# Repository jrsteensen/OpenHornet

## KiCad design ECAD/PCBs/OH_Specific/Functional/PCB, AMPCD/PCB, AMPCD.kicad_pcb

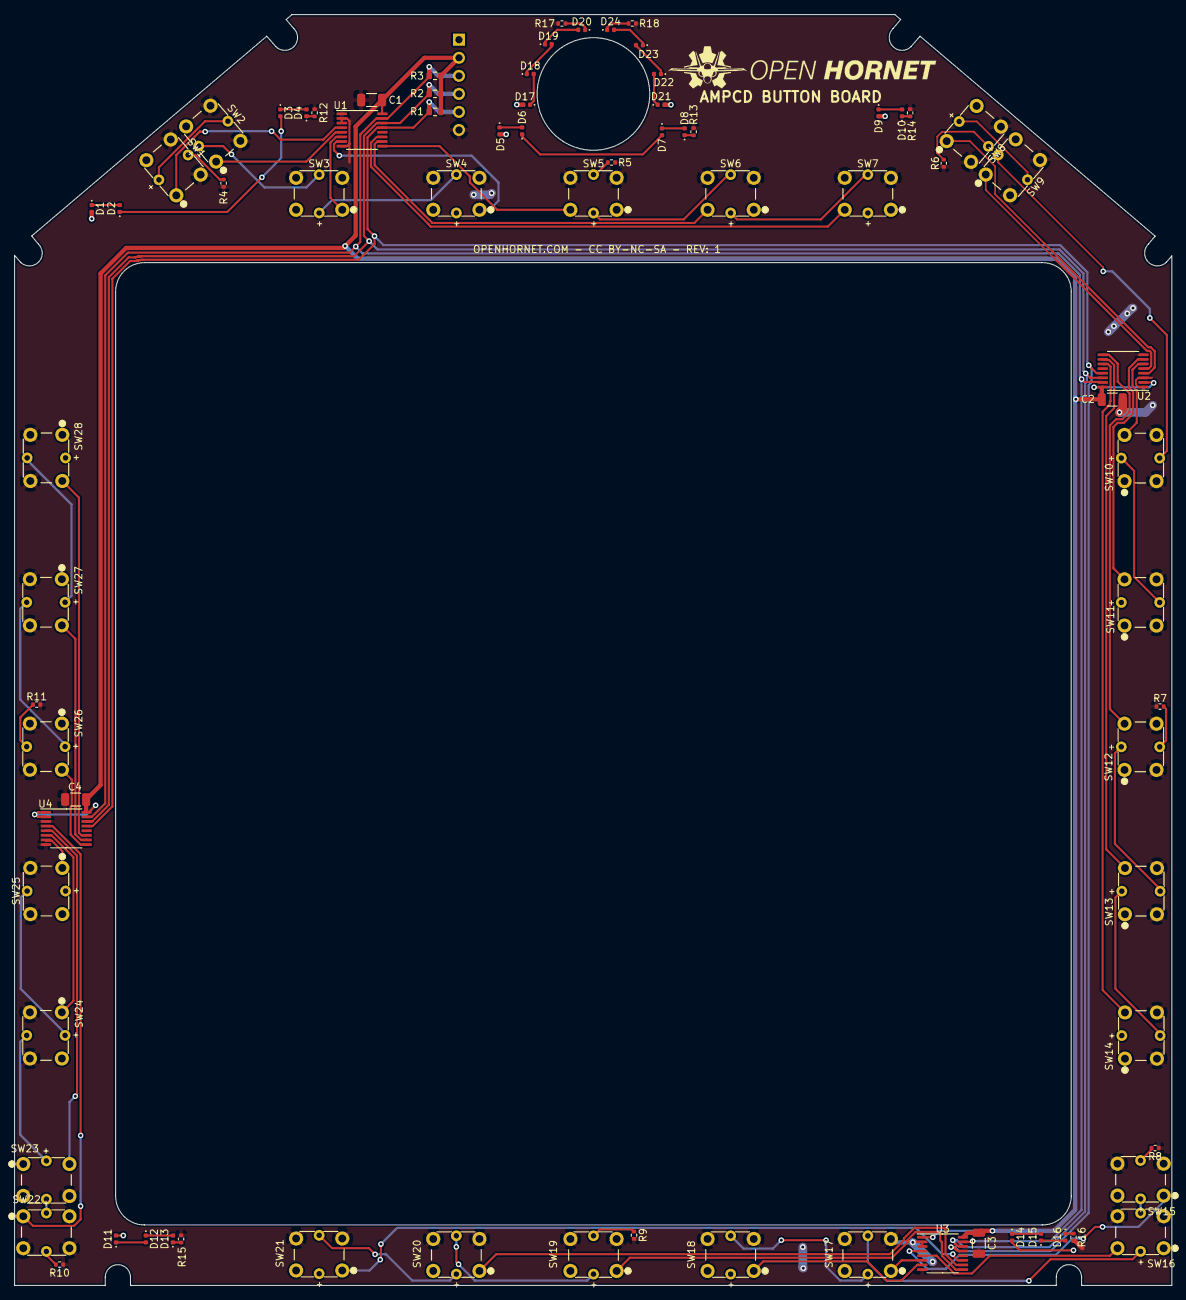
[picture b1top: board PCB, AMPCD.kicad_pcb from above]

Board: 2 copper layers, 162.9 x 178.9 mm, 79 parts (1 on the bottom side), 86 nets.

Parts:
C1, C2, C3, C4: 47uF; C_1206_3216Metric
D1, D2, D3, D4, D5, D6, D7, D8, D9, D10, D11, D12, D13, D14, D15, D16, D17, D18, D19, D20, D21, D22, D23, D24: LED; LED_0402_1005Metric
J1: Conn_01x06; PinHeader_1x06_P2.54mm_Horizontal
R1, R2, R3: 10K; R_0603_1608Metric
R4, R6, R8, R10, R12, R13, R17, R18: 33; R_0402_1005Metric
R5, R7, R9, R11, R15, R16: 150; R_0402_1005Metric
R14: 270; R_0402_1005Metric
SW1, SW2, SW3, SW4, SW5, SW6, SW7, SW8, SW9, SW10, SW11, SW12, SW13, SW14, SW15, SW16, SW17, SW18, SW19, SW20, SW21, SW22, SW23, SW24, SW25, SW26, SW27, SW28: TL1240GQ
U1, U2, U3, U4: TCA9554PWR; TSSOP-16_4.4x5mm_P0.65mm

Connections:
+5V: C1.1, C2.1, C3.1, C4.1, J1.2, R1.1, R2.1, R3.1, U1.16, U2.2, U2.16, U3.1, U3.16, U4.1, U4.2, U4.16
/U1P0: SW1.1, U1.4
/U1P1: SW2.1, U1.5
/U1P2: SW3.1, U1.6
/U1P3: SW4.1, U1.7
/U1P4: SW5.1, U1.9
/U1P5: SW6.1, U1.10
/U1P6: SW7.1, U1.11
/U2P0: SW8.1, U2.4
/U2P1: SW9.1, U2.5
/U2P2: SW10.1, U2.6
/U2P3: SW11.1, U2.7
/U2P4: SW12.1, U2.9
/U2P5: SW13.1, U2.10
/U2P6: SW14.1, U2.11
/U3P0: SW15.1, U3.4
/U3P1: SW16.1, U3.5
/U3P2: SW17.1, U3.6
/U3P3: SW18.1, U3.7
/U3P4: SW19.1, U3.9
/U3P5: SW20.1, U3.10
/U3P6: SW21.1, U3.11
/U4P0: SW22.1, U4.4
/U4P1: SW23.1, U4.5
/U4P2: SW24.1, U4.6
/U4P3: SW25.1, U4.7
/U4P4: SW26.1, U4.9
/U4P5: SW27.1, U4.10
/U4P6: SW28.1, U4.11
GND: C1.2, C2.2, C3.2, C4.2, J1.6, R4.1, R5.1, R6.1, R7.1, R8.1, R9.1, R10.1, R11.1, R12.2, R13.2, R14.2, R15.2, R16.2, R17.2, R18.2, SW1.2, SW2.2, SW3.2, SW4.2, SW5.2, SW6.2, SW7.2, SW8.2, SW9.2, SW10.2, SW11.2, SW12.2, SW13.2, SW14.2, SW15.2, SW16.2, SW17.2, SW18.2, SW19.2, SW20.2, SW21.2, SW22.2, SW23.2, SW24.2, SW25.2, SW26.2, SW27.2, SW28.2, U1.1, U1.2, U1.3, U1.8, U2.1, U2.3, U2.8, U3.2, U3.3, U3.8, U4.3, U4.8
IRQ: J1.5, R1.2, U1.13, U2.13, U3.13, U4.13
unnamed: D1.1, D2.2
unnamed: D2.1, D3.2
unnamed: D3.1, D4.2
unnamed: D4.1, R12.1
unnamed: D5.1, D6.2
unnamed: D6.1, D7.2
unnamed: D7.1, D8.2
unnamed: D8.1, R13.1
unnamed: D10.1, R14.1
unnamed: D9.1, D10.2
unnamed: D11.1, D12.2
unnamed: D12.1, D13.2
unnamed: D13.1, R15.1
unnamed: D14.1, D15.2
unnamed: D15.1, D16.2
unnamed: D16.1, R16.1
unnamed: D17.1, D18.2
unnamed: D18.1, D19.2
unnamed: D19.1, D20.2
unnamed: D20.1, R17.1
unnamed: D21.1, D22.2
unnamed: D22.1, D23.2
unnamed: D23.1, D24.2
unnamed: D24.1, R18.1
unnamed: R4.2, SW1.3
unnamed: R5.2, SW5.3
unnamed: R6.2, SW8.3
unnamed: R7.2, SW12.3
unnamed: R8.2, SW15.3
unnamed: R9.2, SW19.3
unnamed: R10.2, SW22.3
unnamed: R11.2, SW26.3
unnamed: SW1.4, SW2.3
unnamed: SW2.4, SW3.3
unnamed: SW3.4, SW4.3
unnamed: SW5.4, SW6.3
unnamed: SW6.4, SW7.3
unnamed: SW8.4, SW9.3
unnamed: SW9.4, SW10.3
unnamed: SW10.4, SW11.3
unnamed: SW12.4, SW13.3
unnamed: SW13.4, SW14.3
unnamed: SW15.4, SW16.3
unnamed: SW16.4, SW17.3
unnamed: SW17.4, SW18.3
unnamed: SW19.4, SW20.3
unnamed: SW20.4, SW21.3
unnamed: SW22.4, SW23.3
unnamed: SW23.4, SW24.3
unnamed: SW24.4, SW25.3
unnamed: SW26.4, SW27.3
unnamed: SW27.4, SW28.3
SCL: J1.4, R2.2, U1.14, U2.14, U3.14, U4.14
SDA: J1.3, R3.2, U1.15, U2.15, U3.15, U4.15
VCC: D1.2, D5.2, D9.2, D11.2, D14.2, D17.2, D21.2, J1.1, SW4.4, SW7.4, SW11.4, SW14.4, SW18.4, SW21.4, SW25.4, SW28.4

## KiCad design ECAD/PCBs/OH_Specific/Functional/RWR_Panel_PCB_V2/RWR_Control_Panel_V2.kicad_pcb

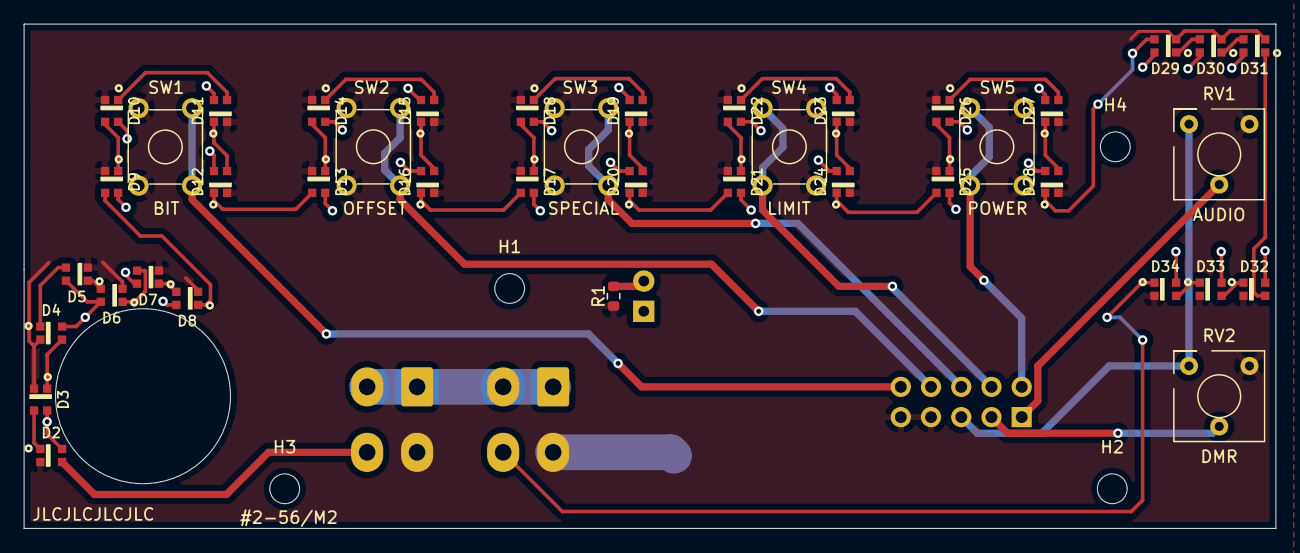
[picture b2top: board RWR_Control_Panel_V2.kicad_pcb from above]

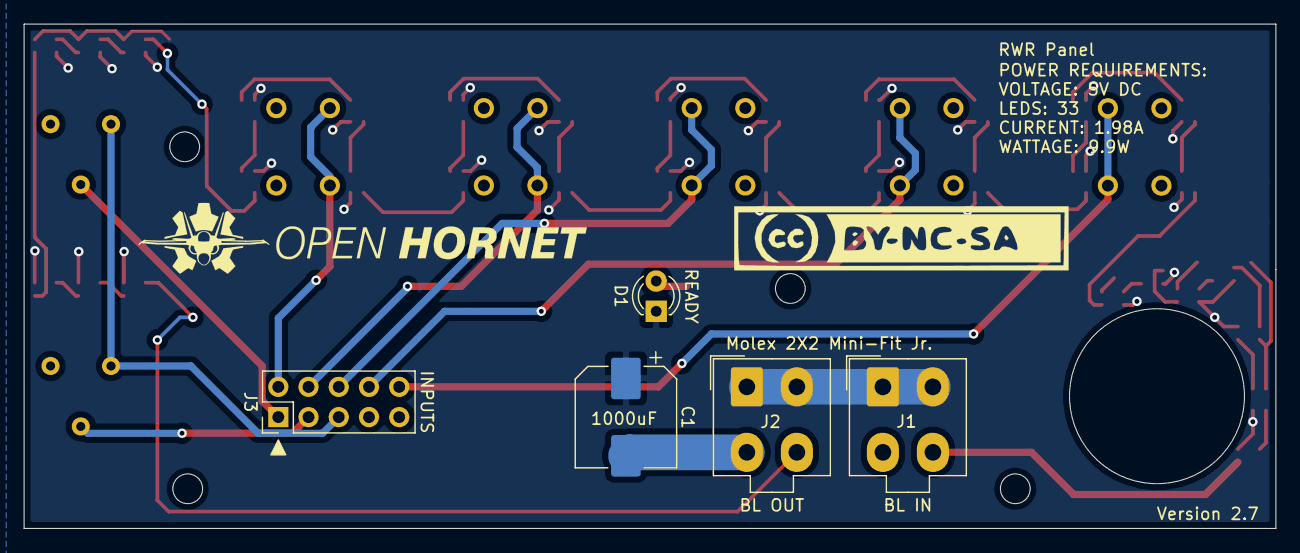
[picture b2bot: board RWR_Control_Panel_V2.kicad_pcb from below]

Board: 2 copper layers, 105.2 x 42.4 mm, 50 parts (5 on the bottom side), 45 nets.

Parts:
C1: 1000 nF; CP_Elec_8x10
D1: READY; LED_D3.0mm
D2, D3, D4, D5, D6, D7, D8, D9, D10, D11, D12, D13, D14, D15, D16, D17, D18, D19, D20, D21, D22, D23, D24, D25, D26, D27, D28, D29, D30, D31, D32, D33, D34: LED; WS2812-2020
H1, H2, H3, H4: MountingHole; MountingHole_2.5mm
J1: BL IN; Molex_Mini-Fit_Jr_5566-04A_2x02_P4.20mm_Vertical
J2: BL OUT; Molex_Mini-Fit_Jr_5566-04A_2x02_P4.20mm_Vertical
J3: INPUTS; PinHeader_2x05_P2.54mm_Vertical
R1: R; R_0603_1608Metric
RV1: AUDIO; Bourns_3310Y
RV2: DMR; Bourns_3310Y
SW1: BIT; SW_TH_Tactile_Omron_B3F-10xx
SW2: OFFSET; SW_TH_Tactile_Omron_B3F-10xx
SW3: SPECIAL; SW_TH_Tactile_Omron_B3F-10xx
SW4: LIMIT; SW_TH_Tactile_Omron_B3F-10xx
SW5: POWER; SW_TH_Tactile_Omron_B3F-10xx

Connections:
+5V: J3.5, RV1.1, RV2.1
/A_AUDIO: J3.1, RV1.2
/A_DMR: J3.3, RV2.2
/BIT_SW: J3.10, SW1.1, SW1.2
/BL_+5V: C1.1, D1.1, D2.4, D3.4, D4.4, D5.4, D6.4, D7.4, D8.4, D9.4, D10.4, D11.4, D12.4, D13.4, D14.4, D15.4, D16.4, D17.4, D18.4, D19.4, D20.4, D21.4, D22.4, D23.4, D24.4, D25.4, D26.4, D27.4, D28.4, D29.4, D30.4, D31.4, D32.4, D33.4, D34.4, J1.1, J1.2, J2.1, J2.2
/BL_DATA1: D9.1, D10.3
/BL_DATA2: D17.1, D18.3
/BL_DATA3: D25.1, D26.3
/BL_DATA4: D33.1, D34.3
/BL_DIN: D2.3, J1.4
/BL_DOUT: D34.1, J2.4
/LIMIT_SW: J3.4, SW4.1, SW4.2
/OFFSET_SW: J3.8, SW2.1, SW2.2
/POWER_SW: J3.2, SW5.1, SW5.2
/SPECIAL_SW: J3.6, SW3.1, SW3.2
GND: C1.2, D2.2, D3.2, D4.2, D5.2, D6.2, D7.2, D8.2, D9.2, D10.2, D11.2, D12.2, D13.2, D14.2, D15.2, D16.2, D17.2, D18.2, D19.2, D20.2, D21.2, D22.2, D23.2, D24.2, D25.2, D26.2, D27.2, D28.2, D29.2, D30.2, D31.2, D32.2, D33.2, D34.2, J1.3, J2.3, J3.7, J3.9, R1.2, RV1.3, RV2.3, SW1.3, SW1.4, SW2.3, SW2.4, SW3.3, SW3.4, SW4.3, SW4.4, SW5.3, SW5.4
unnamed: D1.2, R1.1
unnamed: D2.1, D3.3
unnamed: D3.1, D4.3
unnamed: D4.1, D5.3
unnamed: D5.1, D6.3
unnamed: D6.1, D7.3
unnamed: D7.1, D8.3
unnamed: D8.1, D9.3
unnamed: D10.1, D11.3
unnamed: D11.1, D12.3
unnamed: D12.1, D13.3
unnamed: D13.1, D14.3
unnamed: D14.1, D15.3
unnamed: D15.1, D16.3
unnamed: D16.1, D17.3
unnamed: D18.1, D19.3
unnamed: D19.1, D20.3
unnamed: D20.1, D21.3
unnamed: D21.1, D22.3
unnamed: D22.1, D23.3
unnamed: D23.1, D24.3
unnamed: D24.1, D25.3
unnamed: D26.1, D27.3
unnamed: D27.1, D28.3
unnamed: D28.1, D29.3
unnamed: D29.1, D30.3
unnamed: D30.1, D31.3
unnamed: D31.1, D32.3
unnamed: D32.1, D33.3

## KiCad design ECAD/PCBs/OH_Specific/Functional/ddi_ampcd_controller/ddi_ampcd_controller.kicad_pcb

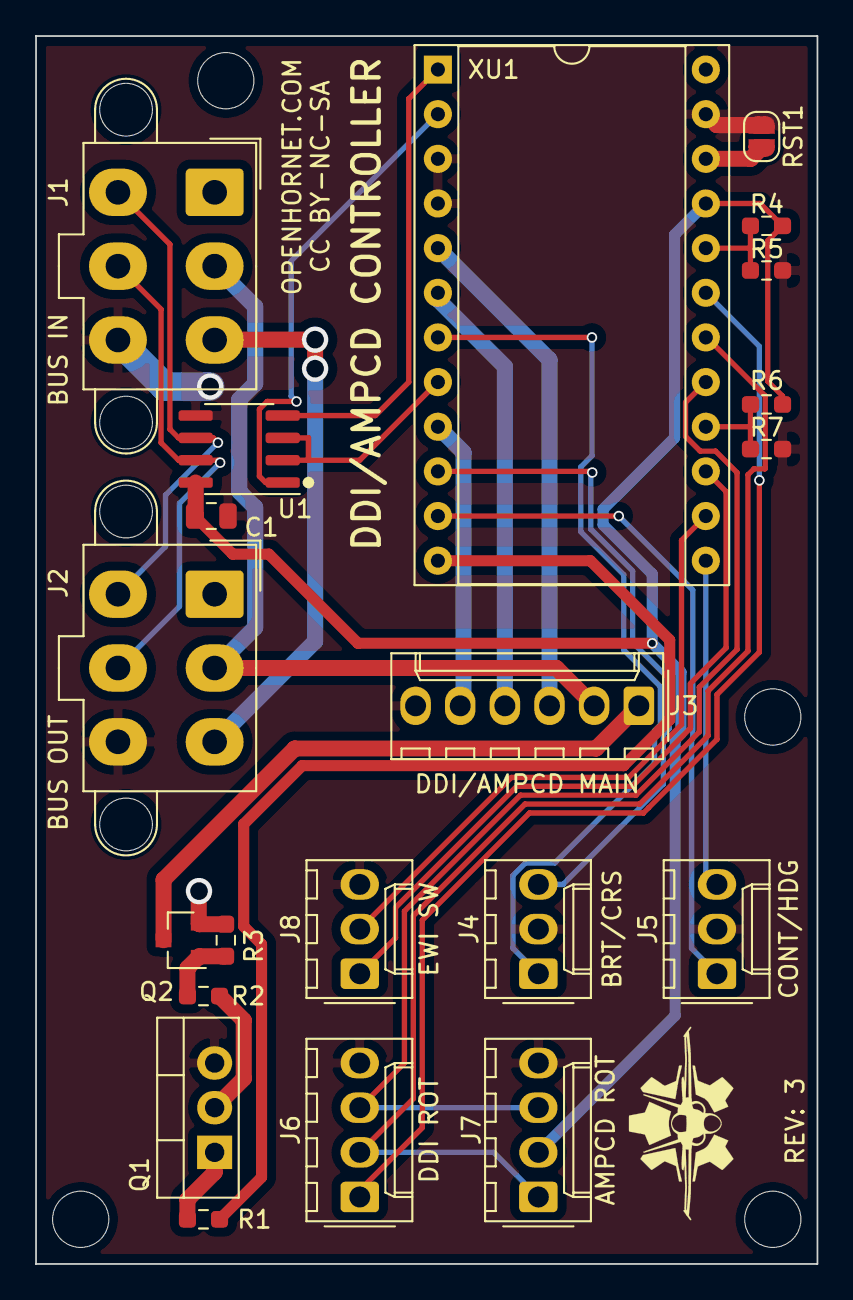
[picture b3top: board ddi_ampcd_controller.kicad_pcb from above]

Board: 2 copper layers, 44.5 x 69.8 mm, 25 parts (0 on the bottom side), 30 nets.

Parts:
C1: 0.1uF; C_0805_2012Metric
H1, H2, H3, H4: MountingHole; MountingHole_3.2mm_M3
J1: BUS IN; Molex_Mini-Fit_Jr_5566-06A2_2x03_P4.20mm_Vertical
J2: BUS OUT; Molex_Mini-Fit_Jr_5566-06A2_2x03_P4.20mm_Vertical
J3: DDI/AMPCD MAIN; Molex_KK-254_AE-6410-06A_1x06_P2.54mm_Vertical
J4: BRT/CRS; Molex_KK-254_AE-6410-03A_1x03_P2.54mm_Vertical
J5: CONT/HDG; Molex_KK-254_AE-6410-03A_1x03_P2.54mm_Vertical
J6: DDI ROT; Molex_KK-254_AE-6410-04A_1x04_P2.54mm_Vertical
J7: AMPCD ROT; Molex_KK-254_AE-6410-04A_1x04_P2.54mm_Vertical
J8: EWI SW; Molex_KK-254_AE-6410-03A_1x03_P2.54mm_Vertical
Q1: IRFB3206PBF; TO-220-3_Vertical
Q2: IRLML6402TRPBF; SOT-23
R1, R2, R3, R4, R5, R6, R7: 10K; R_0603_1608Metric_Pad0.98x0.95mm_HandSolder
RST1: RST; SolderJumper-2_P1.3mm_Open_RoundedPad1.0x1.5mm
U1: MAX487EESA+T; SOIC-8_3.9x4.9mm_P1.27mm
XU1: ProMicro_5V/16Hz; DIP-24_W15.24mm_Socket

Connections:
+5V: C1.1, J7.2, R4.2, R6.2, U1.8, XU1.21
/+3.3V_SUPPLY: J1.3, J2.3
/+5V_SUPPLY: J1.2, J2.2, J3.2
/+12V_PWM: J3.1, Q2.3
/+12V_SUPPLY: J1.1, J2.1, Q2.2, R3.2, XU1.24
/A0: J6.3, J7.3, XU1.17
/A1: J6.2, J7.1, XU1.18
/A2: J6.1, XU1.19
/A3: R4.1, R5.2, XU1.20
/BUS-A: J1.4, J2.4, U1.6
/BUS-B: J1.5, J2.5, U1.7
/D4_A6: J4.1, XU1.7
/D7: J4.3, XU1.10
/D8_A8: J5.1, XU1.11
/D14_MISO: J8.1, XU1.15
/D15_SCK: R6.1, R7.2, XU1.16
/D16_MOSI: J8.2, XU1.14
/RST: RST1.2, XU1.22
/RX1_D0: U1.1, XU1.2
/SDA_D2: J3.3, XU1.5
/TX0_D1: U1.4, XU1.1
/~D5: U1.2, U1.3, XU1.8
/~D6_A7: J3.5, XU1.9
/~D9_A9: R1.1, XU1.12
/~D10_A10: J5.3, XU1.13
/~SCL_D3: J3.4, XU1.6
GND: C1.2, J1.6, J2.6, J3.6, J4.2, J5.2, J6.4, J7.4, J8.3, Q1.3, R5.1, R7.1, RST1.1, U1.5, XU1.3, XU1.4, XU1.23
unnamed: Q1.1, R1.2
unnamed: Q1.2, R2.2
unnamed: Q2.1, R2.1, R3.1

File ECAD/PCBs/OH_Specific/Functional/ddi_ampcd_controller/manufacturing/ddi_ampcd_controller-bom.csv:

Comment,Designator,Footprint,LCSC
"0.1uF","C1","Capacitor_SMD:C_0805_2012Metric_Pad1.15x1.40mm_HandSolder","C49678"
"MountingHole","H1,H2,H3,H4","MountingHole:MountingHole_3.2mm_M3",""
"BUS IN","J1","Connector_Molex:Molex_Mini-Fit_Jr_5569-06A1_2x03_P4.20mm_Horizontal",""
"BUS OUT","J2","Connector_Molex:Molex_Mini-Fit_Jr_5569-06A1_2x03_P4.20mm_Horizontal",""
"Conn_01x06","J3","Connector_Molex:Molex_KK-254_AE-6410-06A_1x06_P2.54mm_Vertical",""
"BRT/CRS","J4","Connector_Molex:Molex_KK-254_AE-6410-03A_1x03_P2.54mm_Vertical",""
"CONT/HDG","J5","Connector_Molex:Molex_KK-254_AE-6410-03A_1x03_P2.54mm_Vertical",""
"DDI ROT","J6","Connector_PinHeader_2.54mm:PinHeader_1x04_P2.54mm_Vertical",""
"AMPCD ROT","J7","Connector_PinHeader_2.54mm:PinHeader_1x04_P2.54mm_Vertical",""
"Digital","P1","Connector_PinSocket_2.54mm:PinSocket_1x15_P2.54mm_Vertical",""
"Analog","P2","Connector_PinSocket_2.54mm:PinSocket_1x15_P2.54mm_Vertical",""
"IRFB3206PBF","Q1","Package_TO_SOT_THT:TO-220-3_Vertical","C2642"
"IRLML6402TRPBF","Q2","Package_TO_SOT_SMD:SOT-23","C2593"
"10K","R1,R2,R3,R4,R5,R6,R7","Resistor_SMD:R_0603_1608Metric_Pad0.98x0.95mm_HandSolder","C25804"
"TP-12","TP1","TestPoint:TestPoint_THTPad_D1.5mm_Drill0.7mm",""
"TP-5V","TP2","TestPoint:TestPoint_THTPad_D1.5mm_Drill0.7mm",""
"TP-3.3V","TP3","TestPoint:TestPoint_THTPad_D1.5mm_Drill0.7mm",""
"TP-GND","TP4","TestPoint:TestPoint_THTPad_D1.5mm_Drill0.7mm",""
"TP-A","TP5","TestPoint:TestPoint_THTPad_D1.5mm_Drill0.7mm",""
"TP-B","TP6","TestPoint:TestPoint_THTPad_D1.5mm_Drill0.7mm",""
"MAX487EESA+T","U1","Package_SO:SOIC-8_3.9x4.9mm_P1.27mm","C116539"

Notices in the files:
ECAD/PCBs/OH_Specific/Functional/PCB, AMPCD/PCB, AMPCD.kicad_pcb:
OPENHORNET.COM - CC BY-NC-SA
OPENHORNET.COM - CC BY-NC-SA - REV: 1
ECAD/PCBs/OH_Specific/Functional/ddi_ampcd_controller/ddi_ampcd_controller.kicad_pcb:
CC BY-NC-SA
